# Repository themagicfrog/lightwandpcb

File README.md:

# lightwandpcb
a pcb with neopixel lights attached and a gyroscope! for arcade and the Trail

also see https://github.com/themagicfrog/lightsaber for final info

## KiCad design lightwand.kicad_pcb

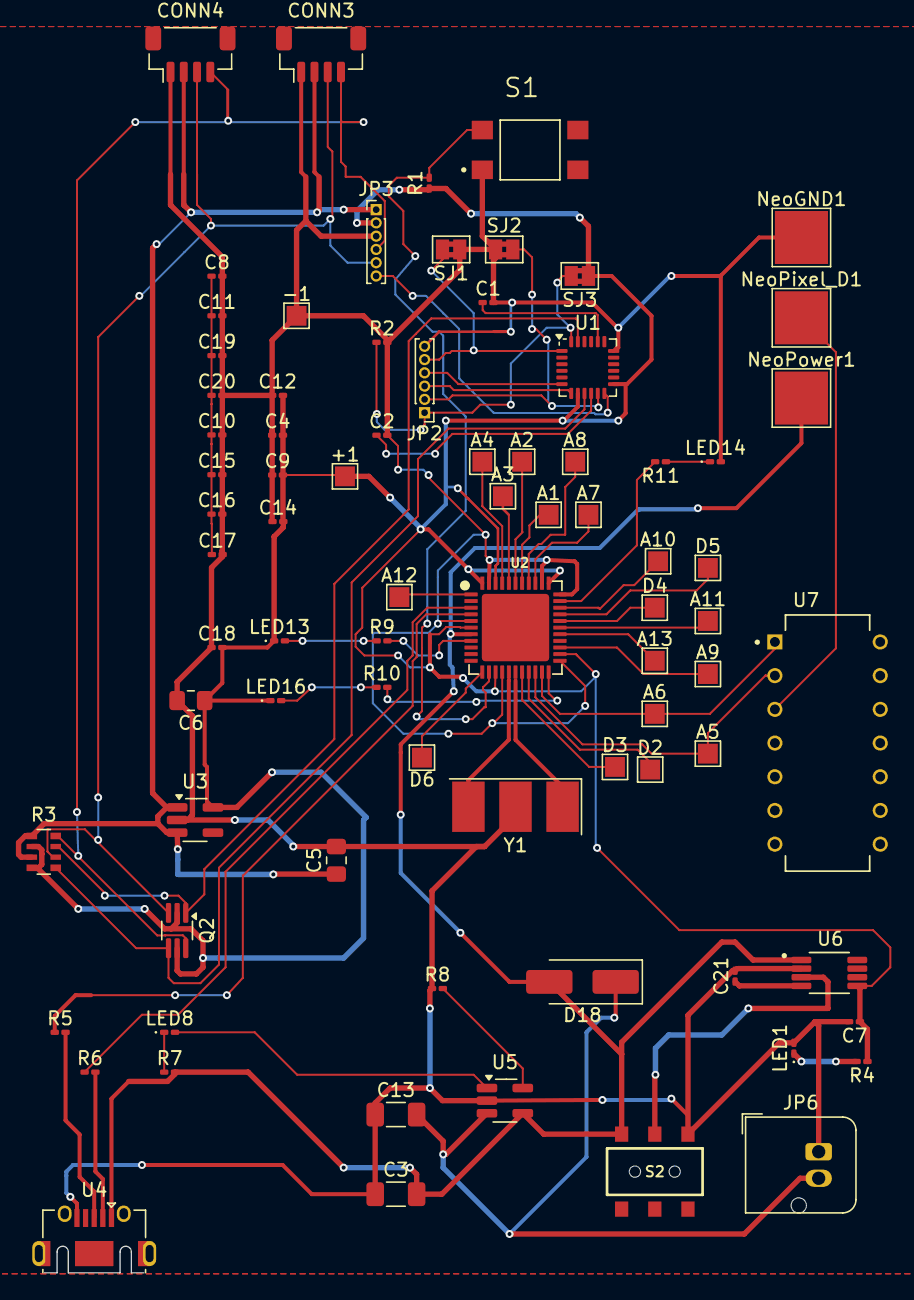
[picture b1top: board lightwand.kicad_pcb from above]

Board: 2 copper layers, 80 parts (0 on the bottom side), 56 nets.

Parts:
+1: SEWTAP9; TestPoint_Pad_1.5x1.5mm
-1: SEWTAP9; TestPoint_Pad_1.5x1.5mm
A1, A2, A3, A4, A5, A6, A7, A8, A9, A10, A11, A12, A13: SEWTAP9; TestPoint_Pad_1.5x1.5mm
C1: 2.2nF; C_0201_0603Metric_Pad0.64x0.40mm_HandSolder
C2, C7: 0.1uF; C_0201_0603Metric_Pad0.64x0.40mm_HandSolder
C3, C13: 4.7uF; C_1206_3216Metric_Pad1.33x1.80mm_HandSolder
C4, C9, C12: .1uF; C_0201_0603Metric_Pad0.64x0.40mm_HandSolder
C5, C6: 10uF; C_0805_2012Metric_Pad1.18x1.45mm_HandSolder
C8, C10, C11, C15, C16, C17, C19, C20: C-EUC0603; C_0201_0603Metric_Pad0.64x0.40mm_HandSolder
C14: 4.7uF; C_0201_0603Metric_Pad0.64x0.40mm_HandSolder
C18: 1uF; C_0201_0603Metric_Pad0.64x0.40mm_HandSolder
C21: 470pF; C_0201_0603Metric_Pad0.64x0.40mm_HandSolder
CONN3, CONN4: STEMMA_I2C_QT; JST_SH_BM04B-SRSS-TB_1x04-1MP_P1.00mm_Vertical
D2, D3, D4, D5, D6: SEWTAP9; TestPoint_Pad_1.5x1.5mm
D18: DIODE-SCHOTTKY-B340A; D_SMA_Handsoldering
JP2: HEADER-1X6ROUND; PinHeader_1x06_P1.00mm_Vertical
JP3: HEADER-1X670MIL; PinHeader_1x06_P1.00mm_Vertical
JP6: M02-JST-2MM-SMT; JST_JWPF_B02B-JWPF-SK-R_1x02_P2.00mm_Vertical
LED1: GREEN; LED_0201_0603Metric_Pad0.64x0.40mm_HandSolder
LED8, LED13, LED14, LED16: RED; LED_0201_0603Metric_Pad0.64x0.40mm_HandSolder
NeoGND1: SEWTAP9; TestPoint_Pad_4.0x4.0mm
NeoPixel_D1: SEWTAP9; TestPoint_Pad_4.0x4.0mm
NeoPower1: SEWTAP9; TestPoint_Pad_4.0x4.0mm
Q2: BSS138; SOT-363_SC-70-6_Handsoldering
R1, R8: 10k; R_0201_0603Metric_Pad0.64x0.40mm_HandSolder
R2, R4: 10K; R_0201_0603Metric_Pad0.64x0.40mm_HandSolder
R3: 10K; R_Array_Convex_4x0603
R5, R6: 22; R_0201_0603Metric_Pad0.64x0.40mm_HandSolder
R7, R9, R10, R11: 330; R_0201_0603Metric_Pad0.64x0.40mm_HandSolder
S1: TL3305BF160QG; SW_TL3305BF160QG
S2: SWITCH-DPDTAYZ0202; AYZ0202
SJ1: CLKIN; SolderJumper-2_P1.3mm_Bridged2Bar_Pad1.0x1.5mm
SJ2: FSYNC; SolderJumper-2_P1.3mm_Bridged2Bar_Pad1.0x1.5mm
SJ3: SOLDERJUMPER; SolderJumper-2_P1.3mm_Bridged2Bar_Pad1.0x1.5mm
U1: MPU-6050; InvenSense_QFN-24_4x4mm_P0.5mm
U2: ATMEGA32U41:1-LESS_PASTE; QFN44G-0.5-7X7MM
U3: AP2112K-3.3; SOT-23-5_HandSoldering
U4: USB-ABCONN-11794; USB_Micro-AB_Molex_47590-0001
U5: MCP73831; SOT-23-5_HandSoldering
U6: MIC5219; SOP65P490X110-8N
U7: 74AHCT125; DIP794W45P254L1930H508Q14
Y1: 8MHz; Resonator_SMD-3Pin_7.2x3.0mm_HandSoldering

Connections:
3.3V: +1.1, C4.2, C6.1, C7.1, C9.2, C12.2, C14.2, C18.2, JP3.2, LED13.1 (A), LED16.1 (A), Q2.2 (G), Q2.5 (G), R1.1, R3.2 (1), R3.4 (1), R4.1, SJ3.1, U1.8 (VLOGIC), U1.13 (VDD), U2.6 (UCAP), U2.14 (VCC@14), U2.24 (AVCC@24), U2.34 (VCC@34), U2.42 (AREF), U2.44 (AVCC@44), U3.5 (OUT), U6.5 (OUT)
5V: C3.2, D18.2 (C), NeoPower1.1, R7.2, S2.1, U2.7 (VBUS), U4.1 (VBUS), U5.4 (VIN), U6.1 (IN)
/AD0: JP2.1, R2.1, SJ3.2, U1.24 (SDA)
/CLKIN: JP2.5, SJ1.2, U1.1 (CLKIN)
/CPOUT: C1.1, U1.20 (CPOUT)
/D+: R5.1, U2.4 (D+)
/D-: R6.1, U2.3 (D-)
/FSYNC_IN: JP2.2, SJ2.2, U1.11 (FSYNC)
/INT: JP3.6, U1.12 (INT)
/REGOUT: C2.1, U1.10 (REGOUT)
/RX_LED: R9.2, U2.8 (PB0(SS))
/SCL: CONN3.4 (SCL), CONN4.4 (SCL), JP3.4, Q2.6 (D), R3.8 (2)
/SCL_3V: Q2.1 (S), R3.7 (2), U1.23 (SCL)
/SCL_EXT: JP2.3, U1.7 (AUX_CL)
/SDA: CONN3.3 (SDA), CONN4.3 (SDA), JP3.5, Q2.3 (D), R3.6 (2)
/SDA_3V: Q2.4 (S), R3.5 (2), U1.9 (AD0)
/SDA_EXT: JP2.4, U1.6 (AUX_DA)
/TX_LED: R10.2, U2.22 (PD5)
/USER_LED: R11.2, U2.32 (PC7)
GND: -1.1, C1.2, C2.2, C3.1, C4.1, C5.2, C6.2, C7.2, C8.2, C9.1, C10.2, C11.2, C12.1, C13.1, C14.1, C15.2, C16.2, C17.2, C18.1, C19.2, C20.2, C21.2, CONN3.1 (GND), CONN4.1 (GND), JP2.6, JP3.3, JP6.1 (2), LED1.2 (C), LED14.2 (C), NeoGND1.1, R2.2, R8.1, S1.1, S2.3, SJ1.1, SJ2.1, U1.18 (GND), U2.5 (UGND), U2.15 (GND@15), U2.23 (GND@23), U2.33 (PE2/~HWB), U2.35 (GND@35), U2.43 (GND@43), U3.2 (GND), U4.5 (GND), U5.2 (VSS), U6.2 (GND), Y1.2
unnamed: LED1.1 (A), R4.2
unnamed: LED8.1 (A), R7.1
unnamed: LED8.2 (C), U5.1 (STAT)
unnamed: LED13.2 (C), R9.1
unnamed: LED14.1 (A), R11.1
unnamed: LED16.2 (C), R10.1
unnamed: NeoPixel_D1.1, U7.3
unnamed: R1.2, S1.3 (2), U2.13 (~RESET)
unnamed: A11.1, U2.28 (PB4(ADC11))
unnamed: D4.1, U2.29 (PB5(ADC12))
unnamed: D5.1, U2.30 (PB6(ADC13))
unnamed: D6.1, U2.12 (PB7)
unnamed: A10.1, U2.31 (PC6)
unnamed: D3.1, U2.18 (PD0(SCL))
unnamed: D2.1, U2.19 (PD1(SDA))
unnamed: A5.1, U2.20 (PD2(RX)), U7.2
unnamed: A6.1, U2.21 (PD3(TX)), U7.1
unnamed: A9.1, U2.25 (PD4(ADC8))
unnamed: A13.1, U2.27 (PD7(ADC10))
unnamed: A12.1, U2.1 (PE6)
unnamed: A4.1, U2.41 (PF0(ADC0))
unnamed: A3.1, U2.40 (PF1(ADC1))
unnamed: A2.1, U2.39 (PF4(ADC4))
unnamed: A1.1, U2.38 (PF5(ADC5))
unnamed: A8.1, U2.37 (PF6(ADC6))
unnamed: A7.1, U2.36 (PF7(ADC7))
unnamed: U2.17 (XTAL1), Y1.1
unnamed: U2.16 (XTAL2), Y1.3
unnamed: R5.2, U4.3 (D+)
unnamed: R6.2, U4.2 (D-)
unnamed: R8.2, U5.5 (PROG)
unnamed: C21.1, U6.4 (BP)
unnamed: S2.2, U6.3 (EN)
VCC: C5.1, CONN3.2 (V+), CONN4.2 (V+), JP3.1, R3.1, R3.3 (1), U3.1 (IN), U3.3 (EN)
VDD: C8.1, C10.1, C11.1, C15.1, C16.1, C17.1, C19.1, C20.1
V_BATT: C13.2, D18.1 (A), JP6.2 (1), U5.3 (VBAT)

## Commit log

2024-07-26 Add capacitorspcb.png
    Finally got the solder paste so I could actually solder on the tiny capacitors! Woohoo!
2024-07-26 Add files via upload
    soldered on all the resistors, which for some reason was a lot harder than the capacitors but now it's done!
2024-07-26 Add files via upload
    more solderinggg
2024-07-26 Add files via upload
    finished soldering!!
2024-07-26 Add files via upload
    working on schematic
2024-07-26 Add files via upload
    designing pcb
2024-07-27 Add files via upload
    i changed the whole concept from lightwand to lighthouse!
2024-08-01 Add files via upload
    more soldering and also had to resolder the usb
2024-08-21 Add files via upload
    decided to use a separate microcontroller and gyroscope wired it up, and also attached it to my board so it's technically "part" of it
